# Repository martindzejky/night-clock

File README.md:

# Night clock

This was my first electronics projects. The goal was to make a "night" clock that would only turn on after clapping. The display was made from orange LEDs to make it suitable for the night.

The project ended up too much for me at the time. I made a proper schematic with all components and designed the PCB layout for a prototype board in KiCad! I used different layers for solder traces and jumper wires. In the end, however, the layout was too complicated and time-consuming. I should have used way more jumper wires, perhaps even utilize wire wrapping wires.

I also did not test the LED display before I started soldering. It later turned out that those 150 ohm resistors were too little and the LEDs were too bright for a night. However, I am very proud that I got the microphone amplifier to work.

All KiCad project files are included in the repository. Here are a few images.

## Schematic

## Pcb

## Photos

I stopped soldering before I could finish the boards. Here are some progress photos.

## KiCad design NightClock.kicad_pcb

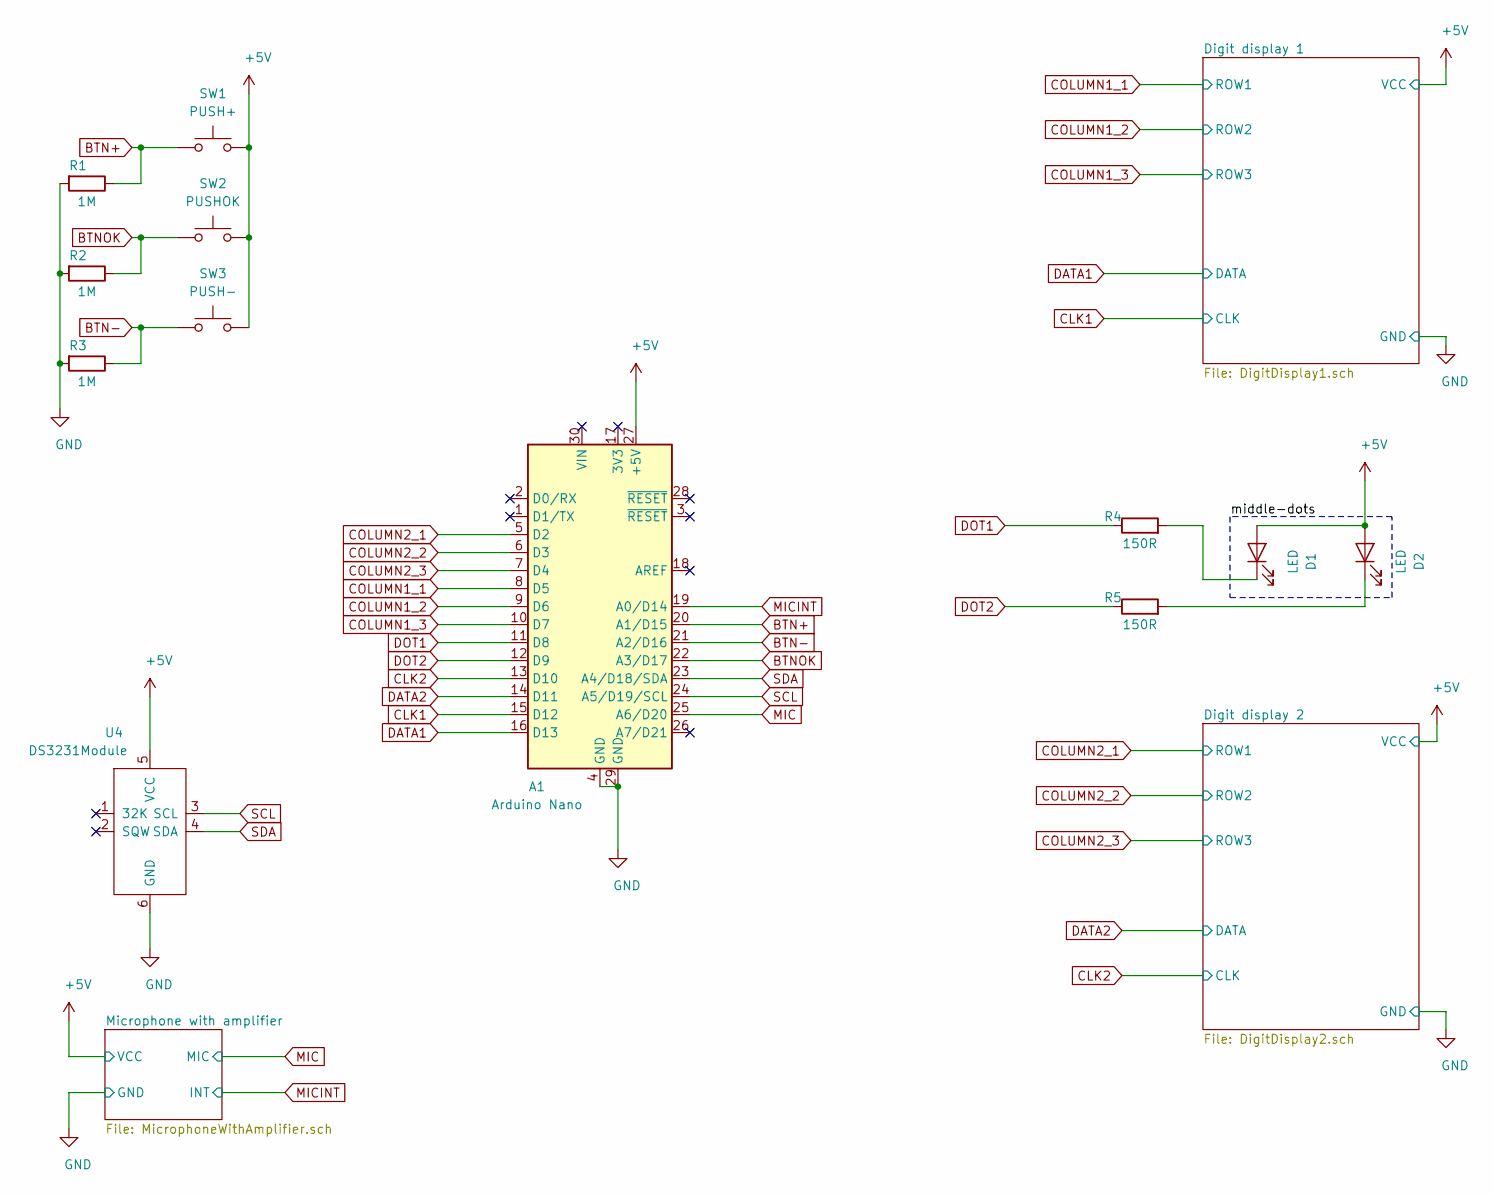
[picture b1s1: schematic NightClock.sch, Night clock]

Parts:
A1: Arduino Nano; Arduino_Nano
D1, D2: LED; LED_D3.0mm
R1, R2, R3: 1M; R_Axial_DIN0207_L6.3mm_D2.5mm_P7.62mm_Horizontal
R4, R5: 150R; R_0805_2012Metric
SW1: PUSH+; PushButtonBlack
SW2: PUSHOK; PushButtonBlack
SW3: PUSH-; PushButtonBlack
U4: DS3231Module; PinSocket_1x06_P2.54mm_Vertical

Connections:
+5V: A1.27 (+5V), D1.2 (A), D2.2 (A), SW1.2, SW2.2, SW3.2, U4.5 (VCC); also elsewhere on the board
BTN+: A1.20 (A1/D15), R1.1, SW1.1
BTN-: A1.21 (A2/D16), R3.1, SW3.1
BTNOK: A1.22 (A3/D17), R2.1, SW2.1
CLK1: A1.15 (D12); also elsewhere on the board
CLK2: A1.13 (D10); also elsewhere on the board
COLUMN1_1: A1.8 (D5); also elsewhere on the board
COLUMN1_2: A1.9 (D6); also elsewhere on the board
COLUMN1_3: A1.10 (D7); also elsewhere on the board
COLUMN2_1: A1.5 (D2); also elsewhere on the board
COLUMN2_2: A1.6 (D3); also elsewhere on the board
COLUMN2_3: A1.7 (D4); also elsewhere on the board
DATA1: A1.16 (D13); also elsewhere on the board
DATA2: A1.14 (D11); also elsewhere on the board
DOT1: A1.11 (D8), R4.1
DOT2: A1.12 (D9), R5.1
GND: A1.4 (GND), A1.29 (GND), R1.2, R2.2, R3.2, U4.6 (GND); also elsewhere on the board
MIC: A1.25 (A6/D20); also elsewhere on the board
MICINT: A1.19 (A0/D14); also elsewhere on the board
unnamed: D1.1 (K), R4.2
unnamed: D2.1 (K), R5.2
SCL: A1.24 (A5/D19/SCL), U4.3 (SCL)
SDA: A1.23 (A4/D18/SDA), U4.4 (SDA)

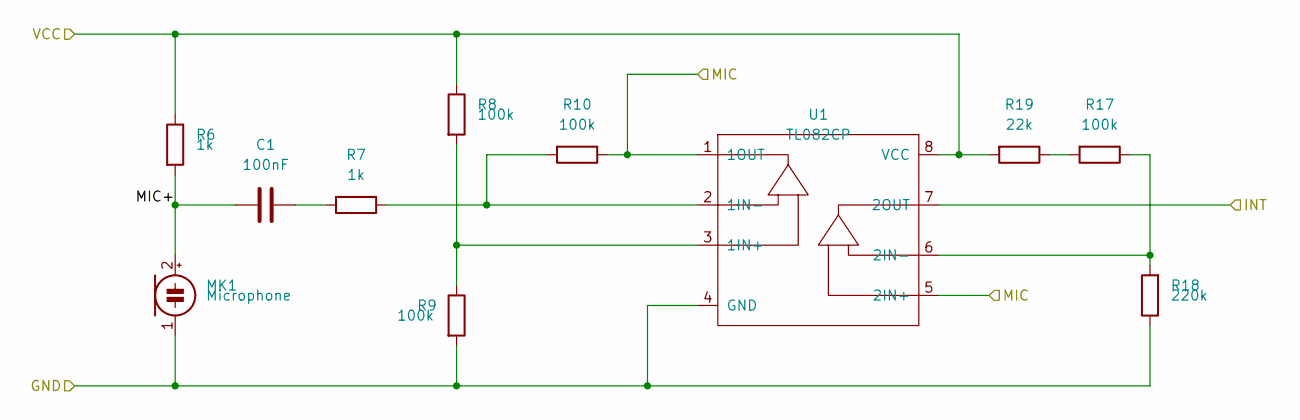
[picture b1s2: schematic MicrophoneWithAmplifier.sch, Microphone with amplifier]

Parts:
C1: 100nF; C_Disc_D3.4mm_W2.1mm_P2.50mm
MK1: Microphone; CP_Radial_Tantal_D9.0mm_P2.50mm
R6, R7: 1k; R_Axial_DIN0207_L6.3mm_D2.5mm_P7.62mm_Horizontal
R8, R9, R10, R17: 100k; R_Axial_DIN0207_L6.3mm_D2.5mm_P7.62mm_Horizontal
R18: 220k; R_Axial_DIN0207_L6.3mm_D2.5mm_P7.62mm_Horizontal
R19: 22k; R_Axial_DIN0207_L6.3mm_D2.5mm_P7.62mm_Horizontal
U1: TL082CP; DIP-8_W7.62mm_Socket

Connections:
+5V: R6.1, R8.1, R19.2, U1.8 (VCC); also elsewhere on the board
/Microphone with amplifier/MIC+: C1.2, MK1.2 (+), R6.2
GND: MK1.1 (-), R9.2, R18.1, U1.4 (GND); also elsewhere on the board
MIC: R10.1, U1.1 (1OUT), U1.5 (2IN+); also elsewhere on the board
MICINT: U1.7 (2OUT); also elsewhere on the board
unnamed: C1.1, R7.2
unnamed: R8.2, R9.1, U1.3 (1IN+)
unnamed: R7.1, R10.2, U1.2 (1IN-)
unnamed: R17.1, R18.2, U1.6 (2IN-)
unnamed: R17.2, R19.1

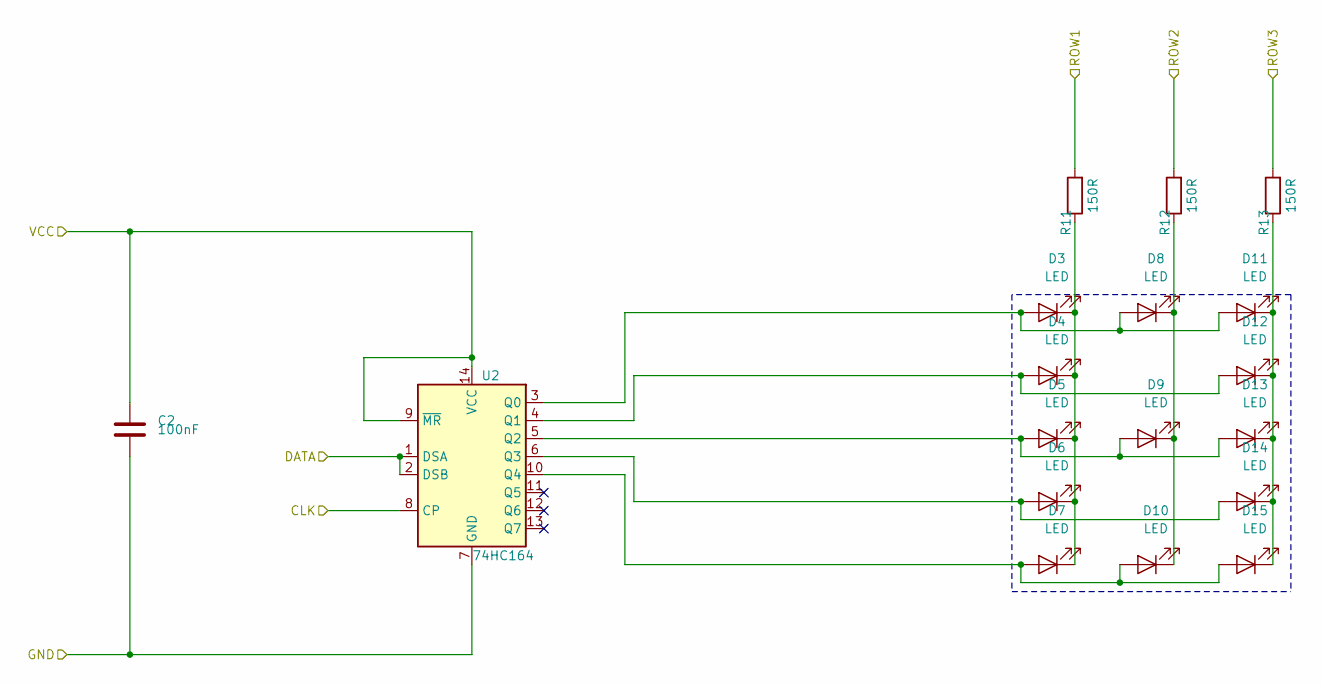
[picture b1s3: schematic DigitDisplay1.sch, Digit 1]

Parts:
C2: 100nF; C_Disc_D3.4mm_W2.1mm_P2.50mm
D3, D4, D5, D6, D7, D8, D9, D10, D11, D12, D13, D14, D15: LED; LED_D3.0mm
R11, R12, R13: 150R; R_0805_2012Metric
U2: 74HC164; DIP-14_W7.62mm_Socket

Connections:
+5V: C2.1, U2.9 (~MR), U2.14 (VCC); also elsewhere on the board
CLK1: U2.8 (CP); also elsewhere on the board
COLUMN1_1: R11.2; also elsewhere on the board
COLUMN1_2: R12.2; also elsewhere on the board
COLUMN1_3: R13.2; also elsewhere on the board
DATA1: U2.1 (DSA), U2.2 (DSB); also elsewhere on the board
GND: C2.2, U2.7 (GND); also elsewhere on the board
unnamed: D3.1 (K), D4.1 (K), D5.1 (K), D6.1 (K), D7.1 (K), R11.1
unnamed: D8.1 (K), D9.1 (K), D10.1 (K), R12.1
unnamed: D7.2 (A), D10.2 (A), D15.2 (A), U2.10 (Q4)
unnamed: D11.1 (K), D12.1 (K), D13.1 (K), D14.1 (K), D15.1 (K), R13.1
unnamed: D3.2 (A), D8.2 (A), D11.2 (A), U2.3 (Q0)
unnamed: D4.2 (A), D12.2 (A), U2.4 (Q1)
unnamed: D5.2 (A), D9.2 (A), D13.2 (A), U2.5 (Q2)
unnamed: D6.2 (A), D14.2 (A), U2.6 (Q3)

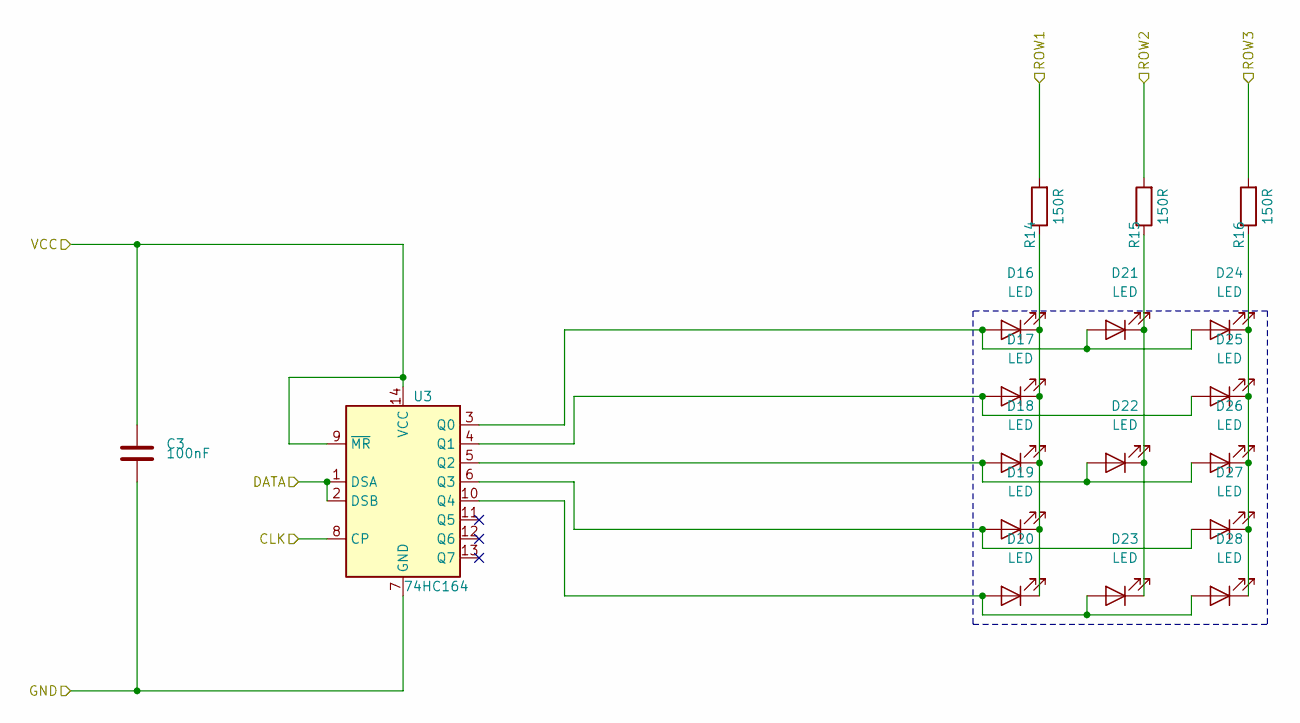
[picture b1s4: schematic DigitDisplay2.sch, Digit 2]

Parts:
C3: 100nF; C_Disc_D3.4mm_W2.1mm_P2.50mm
D16, D17, D18, D19, D20, D21, D22, D23, D24, D25, D26, D27, D28: LED; LED_D3.0mm
R14, R15, R16: 150R; R_0805_2012Metric
U3: 74HC164; DIP-14_W7.62mm_Socket

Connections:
+5V: C3.1, U3.9 (~MR), U3.14 (VCC); also elsewhere on the board
CLK2: U3.8 (CP); also elsewhere on the board
COLUMN2_1: R14.2; also elsewhere on the board
COLUMN2_2: R15.2; also elsewhere on the board
COLUMN2_3: R16.2; also elsewhere on the board
DATA2: U3.1 (DSA), U3.2 (DSB); also elsewhere on the board
GND: C3.2, U3.7 (GND); also elsewhere on the board
unnamed: D16.1 (K), D17.1 (K), D18.1 (K), D19.1 (K), D20.1 (K), R14.1
unnamed: D16.2 (A), D21.2 (A), D24.2 (A), U3.3 (Q0)
unnamed: D17.2 (A), D25.2 (A), U3.4 (Q1)
unnamed: D18.2 (A), D22.2 (A), D26.2 (A), U3.5 (Q2)
unnamed: D19.2 (A), D27.2 (A), U3.6 (Q3)
unnamed: D20.2 (A), D23.2 (A), D28.2 (A), U3.10 (Q4)
unnamed: D21.1 (K), D22.1 (K), D23.1 (K), R15.1
unnamed: D24.1 (K), D25.1 (K), D26.1 (K), D27.1 (K), D28.1 (K), R16.1

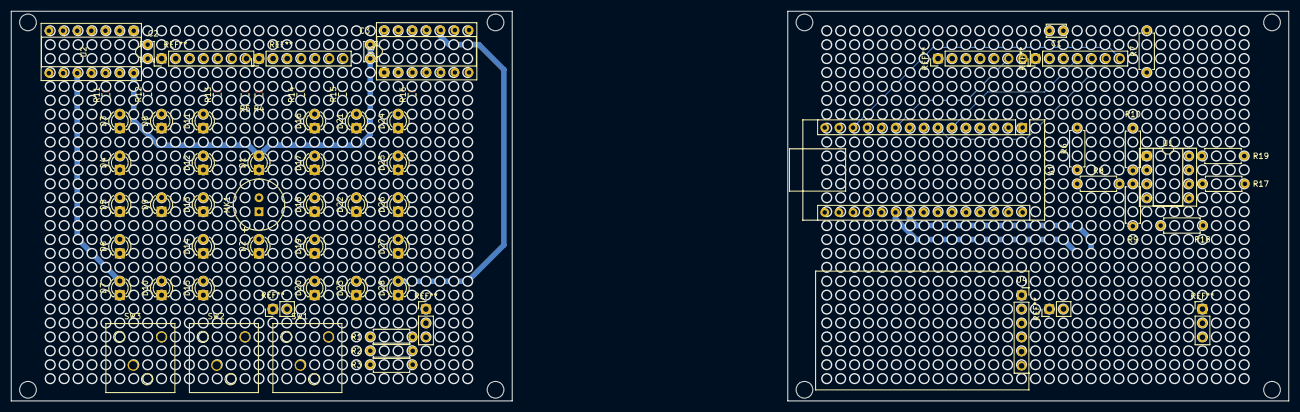
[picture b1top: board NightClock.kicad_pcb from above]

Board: 4 copper layers, 229.5 x 70.0 mm, 59 parts (0 on the bottom side), 45 nets.

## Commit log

2020-04-10 add the project schematic
2020-04-11 add a comparator for setting up an interrupt
2020-04-11 add the RTC module and base prototype pcb layout
2020-04-12 make the pcb design
2020-05-05 add simple arduino program for detecting audio levels
2020-05-05 add images
2020-05-05 add images to README
